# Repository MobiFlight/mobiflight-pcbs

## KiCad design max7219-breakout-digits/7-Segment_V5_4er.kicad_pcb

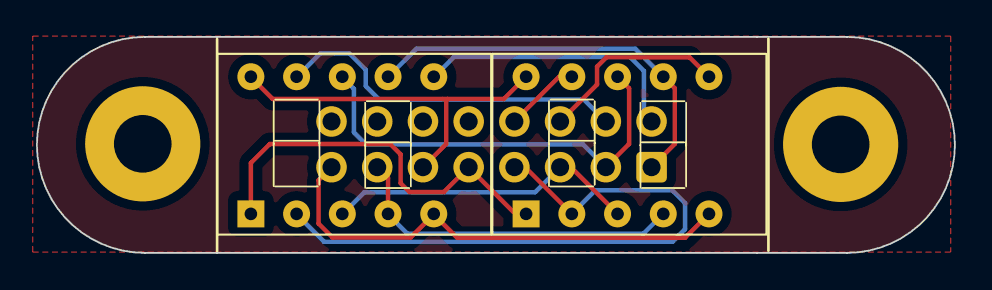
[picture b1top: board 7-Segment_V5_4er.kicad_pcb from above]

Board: 2 copper layers, 51.0 x 12.0 mm, 5 parts (1 on the bottom side), 12 nets.

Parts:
H1, H2: MountingHole 3.2mm; MountingHole_3.2mm_M3_Pad
J1: Conn_02x08_Odd_Even; IDC-Header_2x08_P2.54mm_Vertical
U1, U2: HDSM-443B_CC_2Digit_7Segment_STH; STH_7_2 Digits_0.28_CC

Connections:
/A: J1.1, U1.7 (A), U2.7 (A)
/B: J1.3, U1.8 (B), U2.8 (B)
/C: J1.5, U1.3 (C), U2.3 (C)
/D: J1.7, U1.2 (D), U2.2 (D)
/DIG0: J1.2, U2.6 (CC_DIG2)
/DIG1: J1.4, U2.9 (CC_DIG1)
/DIG2: J1.6, U1.6 (CC_DIG2)
/DIG3: J1.8, U1.9 (CC_DIG1)
/DP: J1.15, U1.5 (DP), U2.5 (DP)
/E: J1.9, U1.1 (E), U2.1 (E)
/F: J1.11, U1.10 (F), U2.10 (F)
/G: J1.13, U1.4 (G), U2.4 (G)

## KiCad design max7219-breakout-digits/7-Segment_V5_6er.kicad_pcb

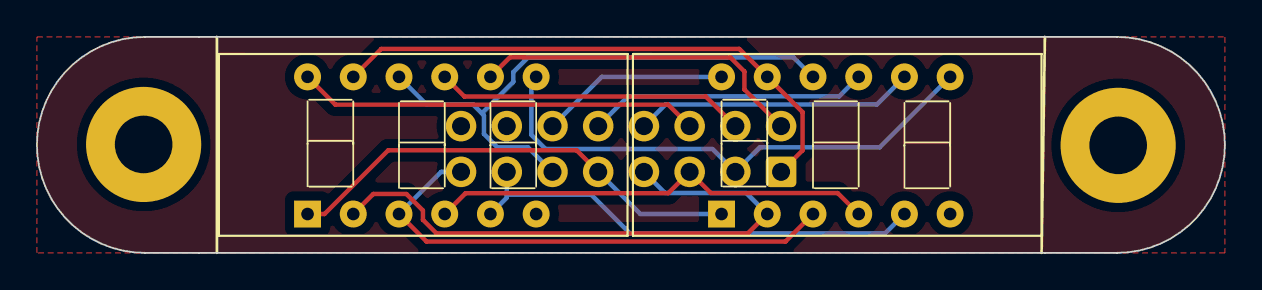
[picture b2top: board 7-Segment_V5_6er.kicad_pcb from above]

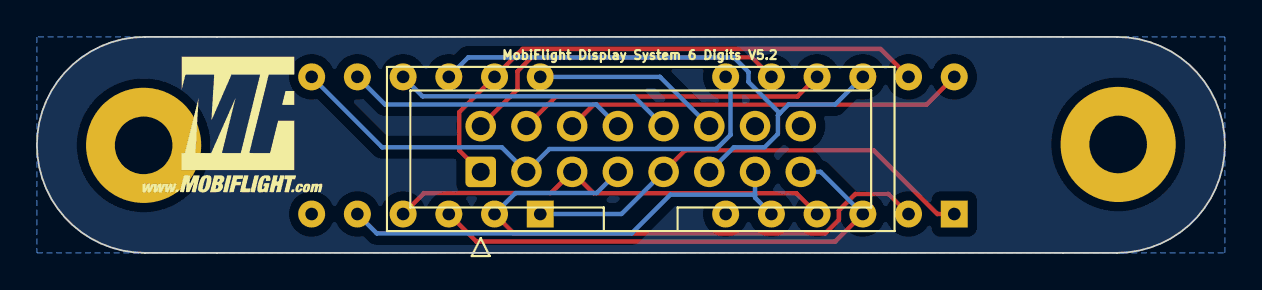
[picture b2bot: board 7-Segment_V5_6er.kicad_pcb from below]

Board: 2 copper layers, 66.0 x 12.0 mm, 6 parts (2 on the bottom side), 14 nets.

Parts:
G2: LOGO; MobiFlight-Logo-Small
H1, H2: MountingHole 3.2mm; MountingHole_3.2mm_M3_Pad
J1: Conn_02x08_Odd_Even; IDC-Header_2x08_P2.54mm_Vertical
U1, U2: 7Segment 3 digit CC_STH; STH_7_3 Digits_0.28_CC

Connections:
/A: J1.1, U1.11 (a), U2.11 (a)
/B: J1.3, U1.7 (b), U2.7 (b)
/C: J1.5, U1.4 (c), U2.4 (c)
/D: J1.7, U1.2 (d), U2.2 (d)
/DIG0: J1.2, U2.8 (CC3)
/DIG1: J1.4, U2.9 (CC2)
/DIG2: J1.6, U2.12 (CC1)
/DIG3: J1.8, U1.8 (CC3)
/DIG4: J1.10, U1.9 (CC2)
/DIG5: J1.12, U1.12 (CC1)
/DP: J1.15, U1.3 (DPX), U2.3 (DPX)
/E: J1.9, U1.1 (e), U2.1 (e)
/F: J1.11, U1.10 (f), U2.10 (f)
/G: J1.13, U1.5 (g), U2.5 (g)

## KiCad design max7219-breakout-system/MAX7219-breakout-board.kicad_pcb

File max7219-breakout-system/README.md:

# MobiFlight MAX7219 Breakout System
The MobiFlight MAX7219 Breakout System board is slightly larger than the display PCBs at 80.0 x 66.0 mm.

Since very few can get by with a MAX chip, this PCB is designed in such a way that it can accommodate up to 4 MAX chips. These chips are already connected in a daisy chain on the PCB. So no one has to worry about where the input or output is, just plug in the IN connector from the Arduino and the 4 MAX chips are connected to each other.

Since up to 8 MAX chips can be connected in a single daisy chain, this PCB was designed in such a way that a 2nd PCB can be connected easily and another 4 MAX chips are connected. Two boards connected, and the daisy chain is complete with all 8 MAX chips.

In case of space problems, this 2nd PCB can be mounted in a different location. It couldn't be easier or more comfortable.

It is therefore still possible to control up to 8 digits per MAX chip and as a daisy chain up to 8 x 8 digits, i.e. 64 digits. Since a Mega Module can control up to 4 separate MAX daisy chains, up to 4 x 64, i.e. 256 digits, are possible per Mobiflight board (e.g., [the MEGA Pro Mini](https://shop.mobiflight.com/product/arduino-mega-2560-pro-mini)).

## Connectors
There are two box headers (straight type) assigned to each MAX chip for more flexibility and efficient use.

Having two connectors allows for the possibility of dividing the 8 digits of a MAX chip between two groups of digts:
* 2 x 4 digits, 
* 1 x 3 and 1 x 5 digits,
* 1 x 6 digits, and 
* 2 x 3 digits. 

Not all 8 digits of a MAX chip have to be used. Also, the digits do not have to be distributed evenly across the MAX chips.

Between the plugs there are designations such as DIG 0-3, DIG 0-5 and DIG 4-7. This specifies how the digits are to be distributed to the plugs and thus the displays.

If, for example, 6 digits are plugged into J2, digits 0-5 are occupied. This means that digits 6 and 7 on connector J3 would remain free because, as is well known, there are no 2-digit displays in our cockpits. The smallest display unit would therefore be 3 digits.

This also applies to connectors J4 and J5, J6 and J7 and J8 and J9.

Displays with 3, 4, 5 and 6 digits can be plugged into the connectors J2, J4, J6 and J8. Displays with 3 or 4 digits can be plugged into connectors J3, J5, J7 and J9, but not more than 8 digits in total. A combination of 5 or 6 digits on J2 and 4 digits on J3 at the same time is therefore not possible.

## Prototyping board

With the 5-pin XH JST cable that is provided, a connection to the prototyping board is simple.

> [!NOTE]
> Starting with v2.0, the pin sequence is the same for both boards, the prototyping board and the MAX7219 breakout board.

## Daisy chain mode

You can connect two boards together and take advantage of the daisy chain capability. Two boards is the maximum, only up to 8 MAX7219 chips can be chained. This is a limitation of the MAX7219 chip itself.

## External Power supply
The power supply with +5V should be provided via a separate power pack, since a MAX chip can consume between 80 and 120 mA of current and thus the Mega Module or a USB interface (maximum 500 mA with USB 2.x or 900 mA with USB 3 .x) can be overloaded.

> [!NOTE]
> When using external power, set the blue jumper to the "EXT" position, otherwise use "INT" position.

## Board overview

### MAX7219 - IC1-4
The IC socket and the 4 MAX7219 chips

### Connector - J2-J9
The connectors to connect the flat ribbon cables

### IN-connectors J1+J11
The pins that are connected to pins on the MobiFlight board.

* Pin 1 - VCC
* Pin 2 - GND
* Pin 3 - DIN
* Pin 4 - CS
* PIN 5 - CLK

### OUT-connectors J10+J12
* Pin 1 - VCC
* Pin 2 - GND
* Pin 3 - DOUT
* Pin 4 - CS
* PIN 5 - CLK

## Assembly instructions
1. Solder resistors (10kOhm) to the top of the PCB
1. Solder the capacitors (100nF) to the top of the PCB
1. Solder the Max7219 IC sockets to the top of the PCB
1. Solder the XH JST connectors to the top of the PCB
1. Solder the 8x2 connectors to the top of the PCB
1. Insert the MAX7219 Chips into the sockets, watch out for correct orientation

## MobiFlight Configuration
### Device configuration
See [general documentation for more information](https://docs.mobiflight.com/devices/seven-segment-display/configuring-output/) on how to configure the 7-segment displays.

### Output config

#### Special feature with 3 digit displays
A special feature is the 3 digit displays. If 2 x 3 digits are used on connectors J2 and J3 in MobiFlight, care must be taken to ensure that they are each offset by one digit. A 3-digit display on J2 would therefore occupy digits 1, 2 and 3 in MobiFlight and on J3 digits 5, 6 and 7 in MobiFlight.

Normally, assignment of the 3 digit displays in MobiFlight when 3 digit displays are used looks like this:

With the breakout board, using two 3-digit displays looks like this:

This also applies if 5 digits are assigned to J2, then only 3 digits can be assigned to J3. But since digit 4 is parallel on J2 and J3, it is imperative to start with digit 5 on J3 for a 3-digit display (digit 5, 6 and 7). Nothing has to be taken into account when wiring, because the 3-digit PCBs already take this into account, regardless of whether they are plugged into J2 or J3.

This may look confusing at first glance, but once you look at the constellation, it quickly becomes clear that this is the only way to ensure optimum utilization without having to plug in jumpers or the like.

## Additional information

### Orientation and pin assignments

The soldering points, which are square, always designate pin 1 of the corresponding component.
After pin 1, the row continues in ascending order with pins 3, 5, 7, 9, 11, 13 and 15. The other row therefore has pins 2, 4, 6, 8, 10, 12, 14 and 16.

With the connectors J2, J4, J6 and J8 the cathodes of the displays are connected in ascending order from pin 2. So pin 2 = cathode of digit 0, pin 4 = cathode of digit 1, pin 6 = cathode 3, pin 8 = cathode 4, pin 10 = cathode 5 and pin 12 = cathode 6. Pins 14 and 16 are on the connectors always free with an even pin number.

The segments were connected to the odd pins. Pin 1 = Segment A, Pin 3 = Segment B, Pin 5 = Segment C, Pin 7 = Segment D, Pin 9 = Segment E, Pin 11 = Segment F, Pin 13 = Segment G and Pin 15 of the DP.

The situation is similar for connectors J3, J5, J7 and J9.
Pin 2 = cathode 4, pin 4 = cathode 5, pin 6 = cathode 6 and pin 8 = cathode 7. Pins 10, 12, 14 and 16 are not used.
In the case of the segments, these are assigned even numbers, as is the case with the plugs.

### Top side with components

### Bottom side

### Schematic

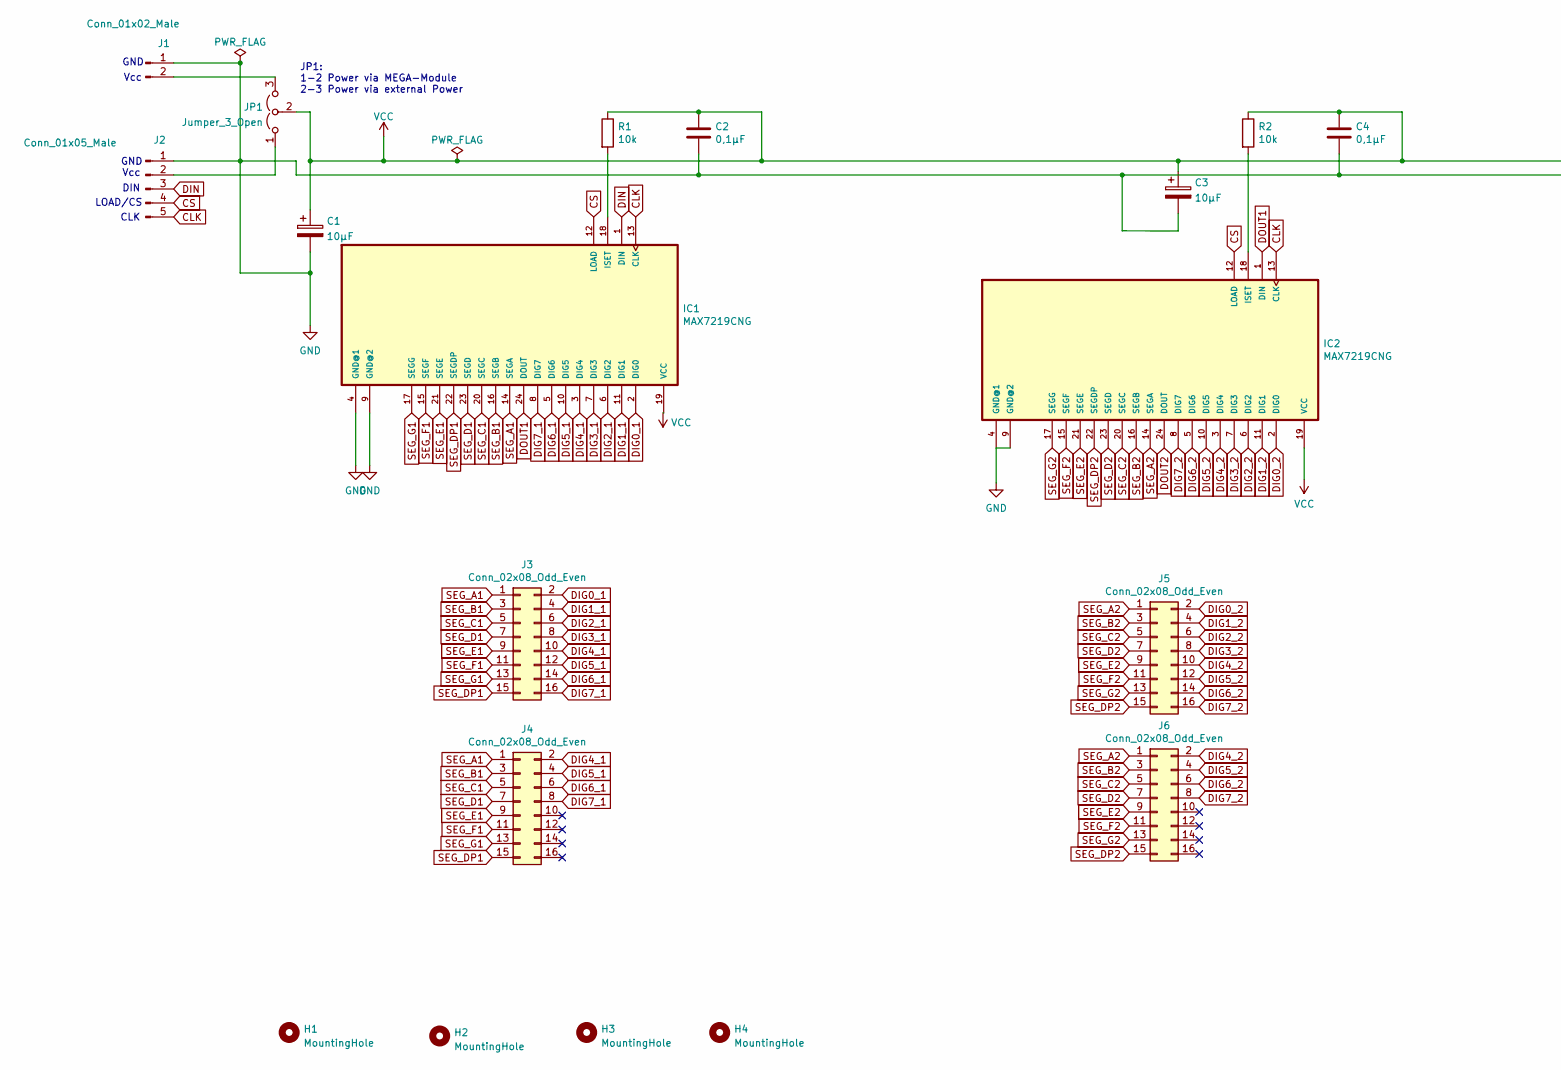
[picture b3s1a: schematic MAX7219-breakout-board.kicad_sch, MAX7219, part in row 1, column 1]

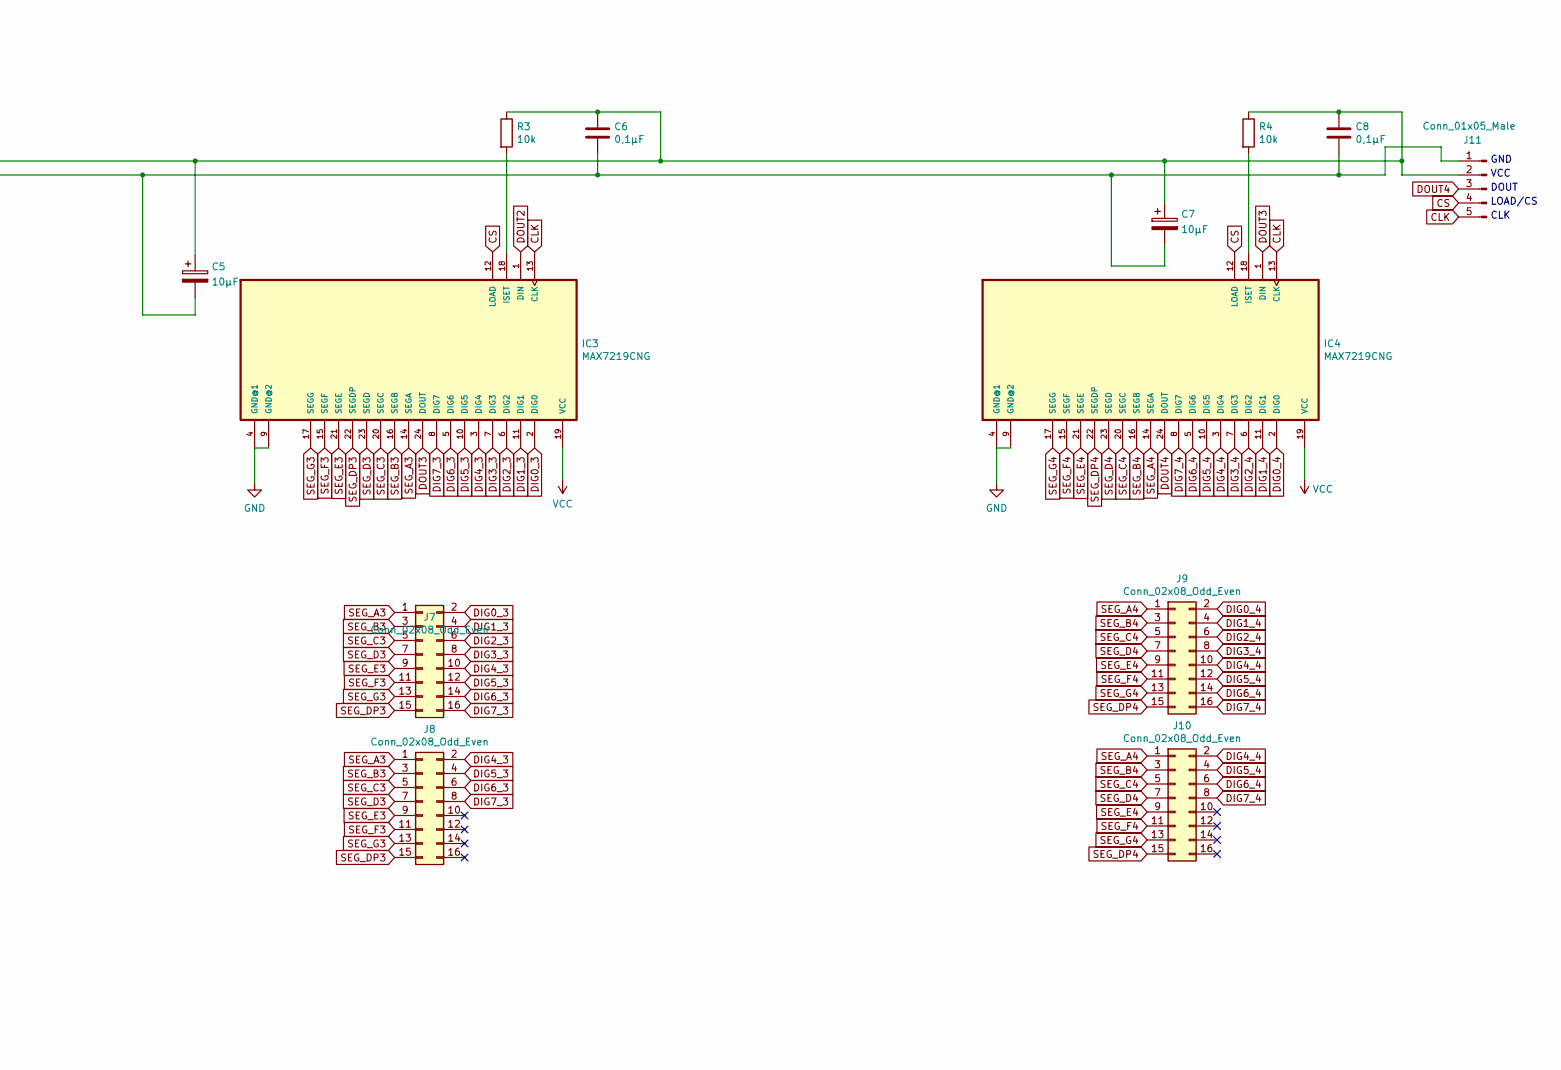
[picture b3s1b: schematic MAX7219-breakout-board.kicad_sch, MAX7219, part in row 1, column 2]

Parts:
C1, C3, C5, C7: 10µF; CP_Radial_D5.0mm_P2.50mm
C2, C4, C6, C8: 0,1µF; C_Disc_D5.0mm_W2.5mm_P5.00mm
H1, H2, H3, H4: MountingHole; MountingHole_3.2mm_M3_Pad
IC1, IC2, IC3, IC4: MAX7219CNG; DIP-24_W7.62mm
J1: Conn_01x02_Male; JST_XH_B2B-XH-A_1x02_P2.50mm_Vertical
J2, J11: Conn_01x05_Male; JST_XH_B5B-XH-A_1x05_P2.50mm_Vertical
J3, J4, J5, J6, J7, J8, J9, J10: Conn_02x08_Odd_Even; IDC-Header_2x08_P2.54mm_Vertical
JP1: Jumper_3_Open; PinHeader_1x03_P2.54mm_Vertical
R1, R2, R3, R4: 10k; R_Axial_DIN0204_L3.6mm_D1.6mm_P7.62mm_Horizontal

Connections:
CLK: IC1.13 (CLK), IC2.13 (CLK), IC3.13 (CLK), IC4.13 (CLK), J2.5, J11.5
CS: IC1.12 (LOAD), IC2.12 (LOAD), IC3.12 (LOAD), IC4.12 (LOAD), J2.4, J11.4
DIG0_1: IC1.2 (DIG0), J3.2
DIG0_2: IC2.2 (DIG0), J5.2
DIG0_3: IC3.2 (DIG0), J7.2
DIG0_4: IC4.2 (DIG0), J9.2
DIG1_1: IC1.11 (DIG1), J3.4
DIG1_2: IC2.11 (DIG1), J5.4
DIG1_3: IC3.11 (DIG1), J7.4
DIG1_4: IC4.11 (DIG1), J9.4
DIG2_1: IC1.6 (DIG2), J3.6
DIG2_2: IC2.6 (DIG2), J5.6
DIG2_3: IC3.6 (DIG2), J7.6
DIG2_4: IC4.6 (DIG2), J9.6
DIG3_1: IC1.7 (DIG3), J3.8
DIG3_2: IC2.7 (DIG3), J5.8
DIG3_3: IC3.7 (DIG3), J7.8
DIG3_4: IC4.7 (DIG3), J9.8
DIG4_1: IC1.3 (DIG4), J3.10, J4.2
DIG4_2: IC2.3 (DIG4), J5.10, J6.2
DIG4_3: IC3.3 (DIG4), J7.10, J8.2
DIG4_4: IC4.3 (DIG4), J9.10, J10.2
DIG5_1: IC1.10 (DIG5), J3.12, J4.4
DIG5_2: IC2.10 (DIG5), J5.12, J6.4
DIG5_3: IC3.10 (DIG5), J7.12, J8.4
DIG5_4: IC4.10 (DIG5), J9.12, J10.4
DIG6_1: IC1.5 (DIG6), J3.14, J4.6
DIG6_2: IC2.5 (DIG6), J5.14, J6.6
DIG6_3: IC3.5 (DIG6), J7.14, J8.6
DIG6_4: IC4.5 (DIG6), J9.14, J10.6
DIG7_1: IC1.8 (DIG7), J3.16, J4.8
DIG7_2: IC2.8 (DIG7), J5.16, J6.8
DIG7_3: IC3.8 (DIG7), J7.16, J8.8
DIG7_4: IC4.8 (DIG7), J9.16, J10.8
DIN: IC1.1 (DIN), J2.3
DOUT1: IC1.24 (DOUT), IC2.1 (DIN)
DOUT2: IC2.24 (DOUT), IC3.1 (DIN)
DOUT3: IC3.24 (DOUT), IC4.1 (DIN)
DOUT4: IC4.24 (DOUT), J11.3
GND: C1.2, C2.2, C3.2, C4.2, C5.2, C6.2, C7.2, C8.2, IC1.4 (GND@1), IC1.9 (GND@2), IC2.4 (GND@1), IC2.9 (GND@2), IC3.4 (GND@1), IC3.9 (GND@2), IC4.4 (GND@1), IC4.9 (GND@2), J1.1, J2.1, J11.1
unnamed: IC1.18 (ISET), R1.2
unnamed: IC2.18 (ISET), R2.2
unnamed: IC3.18 (ISET), R3.2
unnamed: IC4.18 (ISET), R4.2
unnamed: J1.2, JP1.3 (B)
unnamed: J2.2, JP1.1 (A)
SEG_A1: IC1.14 (SEGA), J3.1, J4.1
SEG_A2: IC2.14 (SEGA), J5.1, J6.1
SEG_A3: IC3.14 (SEGA), J7.1, J8.1
SEG_A4: IC4.14 (SEGA), J9.1, J10.1
SEG_B1: IC1.16 (SEGB), J3.3, J4.3
SEG_B2: IC2.16 (SEGB), J5.3, J6.3
SEG_B3: IC3.16 (SEGB), J7.3, J8.3
SEG_B4: IC4.16 (SEGB), J9.3, J10.3
SEG_C1: IC1.20 (SEGC), J3.5, J4.5
SEG_C2: IC2.20 (SEGC), J5.5, J6.5
SEG_C3: IC3.20 (SEGC), J7.5, J8.5
SEG_C4: IC4.20 (SEGC), J9.5, J10.5
SEG_D1: IC1.23 (SEGD), J3.7, J4.7
SEG_D2: IC2.23 (SEGD), J5.7, J6.7
SEG_D3: IC3.23 (SEGD), J7.7, J8.7
SEG_D4: IC4.23 (SEGD), J9.7, J10.7
SEG_DP1: IC1.22 (SEGDP), J3.15, J4.15
SEG_DP2: IC2.22 (SEGDP), J5.15, J6.15
SEG_DP3: IC3.22 (SEGDP), J7.15, J8.15
SEG_DP4: IC4.22 (SEGDP), J9.15, J10.15
SEG_E1: IC1.21 (SEGE), J3.9, J4.9
SEG_E2: IC2.21 (SEGE), J5.9, J6.9
SEG_E3: IC3.21 (SEGE), J7.9, J8.9
SEG_E4: IC4.21 (SEGE), J9.9, J10.9
SEG_F1: IC1.15 (SEGF), J3.11, J4.11
SEG_F2: IC2.15 (SEGF), J5.11, J6.11
SEG_F3: IC3.15 (SEGF), J7.11, J8.11
SEG_F4: IC4.15 (SEGF), J9.11, J10.11
SEG_G1: IC1.17 (SEGG), J3.13, J4.13
SEG_G2: IC2.17 (SEGG), J5.13, J6.13
SEG_G3: IC3.17 (SEGG), J7.13, J8.13
SEG_G4: IC4.17 (SEGG), J9.13, J10.13
VCC: C1.1, C2.1, C3.1, C4.1, C5.1, C6.1, C7.1, C8.1, IC1.19 (VCC), IC2.19 (VCC), IC3.19 (VCC), IC4.19 (VCC), J11.2, JP1.2 (C), R1.1, R2.1, R3.1, R4.1

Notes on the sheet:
Vcc
JP1: 1-2 Power via MEGA-Module 2-3 Power via external Power
VCC
CLK
GND
LOAD/CS
DOUT
DIN

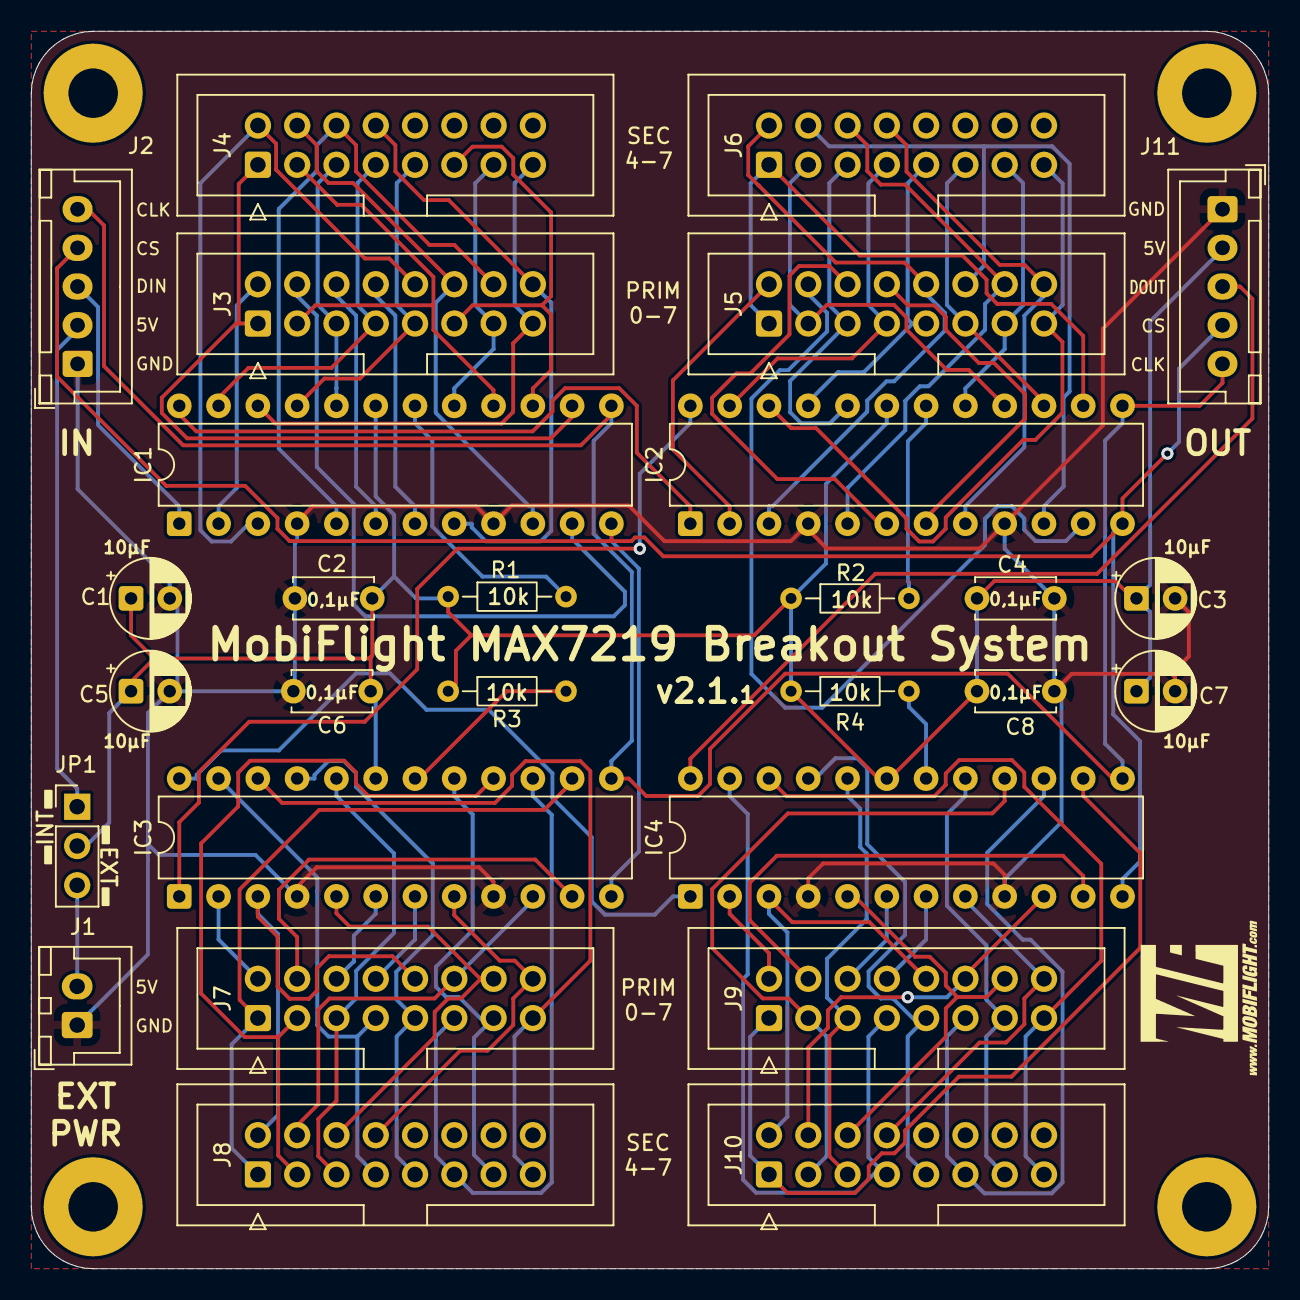
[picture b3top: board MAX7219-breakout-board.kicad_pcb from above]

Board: 2 copper layers, 80.0 x 80.0 mm, 34 parts (1 on the bottom side), 79 nets.

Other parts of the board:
G1: LOGO; MobiFlight_250x250
G2: LOGO; MobiFlight-Logo-Small

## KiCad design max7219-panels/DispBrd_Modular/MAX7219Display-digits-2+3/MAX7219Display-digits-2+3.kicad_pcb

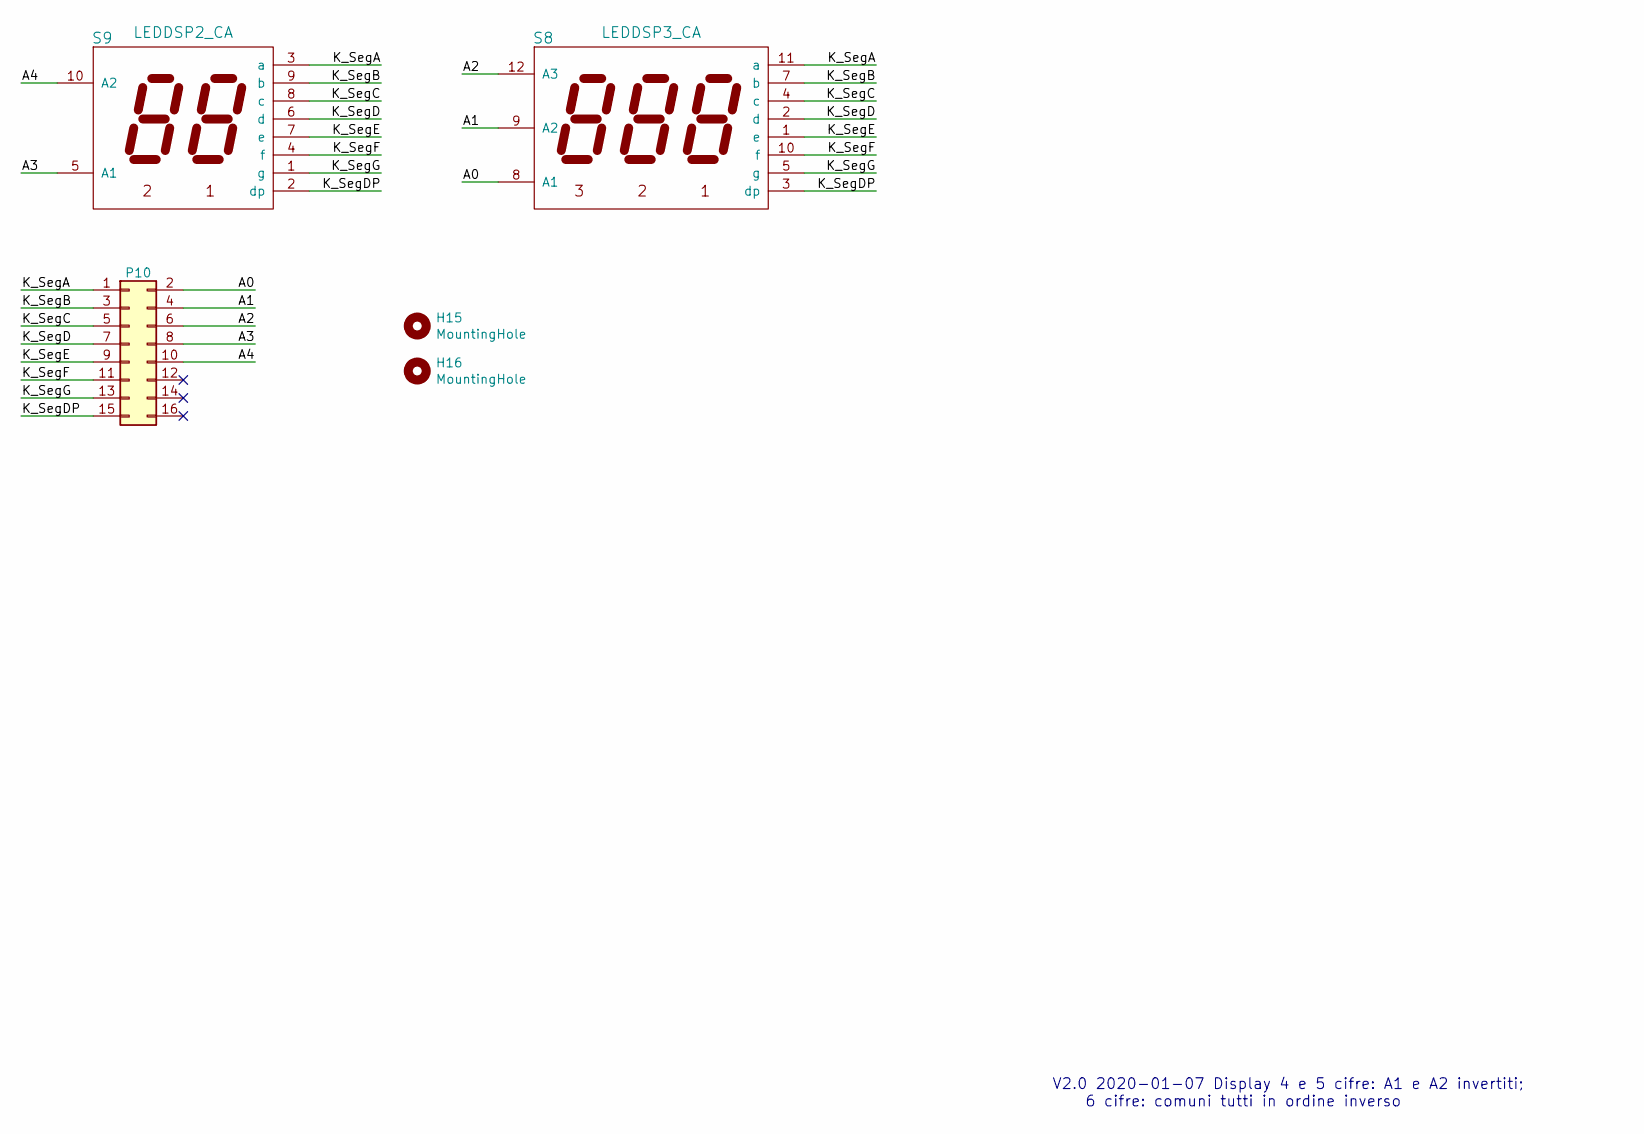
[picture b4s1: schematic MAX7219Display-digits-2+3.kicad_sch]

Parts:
H15, H16: MountingHole; Hole3mm
P10: Conn_02x08_Odd_Even; IDC-Header_2x08_P2.54mm_Vertical
S8: LEDDSP3_CA; Disp7s3x_036
S9: LEDDSP2_CA; Disp7s2x_036

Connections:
/A0: P10.2, S8.8 (A1)
/A1: P10.4, S8.9 (A2)
/A2: P10.6, S8.12 (A3)
/A3: P10.8, S9.5 (A1)
/A4: P10.10, S9.10 (A2)
/K_SegA: P10.1, S8.11 (a), S9.3 (a)
/K_SegB: P10.3, S8.7 (b), S9.9 (b)
/K_SegC: P10.5, S8.4 (c), S9.8 (c)
/K_SegD: P10.7, S8.2 (d), S9.6 (d)
/K_SegDP: P10.15, S8.3 (dp), S9.2 (dp)
/K_SegE: P10.9, S8.1 (e), S9.7 (e)
/K_SegF: P10.11, S8.10 (f), S9.4 (f)
/K_SegG: P10.13, S8.5 (g), S9.1 (g)

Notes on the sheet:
V2.0 2020-01-07 Display 4 e 5 cifre: A1 e A2 invertiti; 6 cifre: comuni tutti in ordine inverso

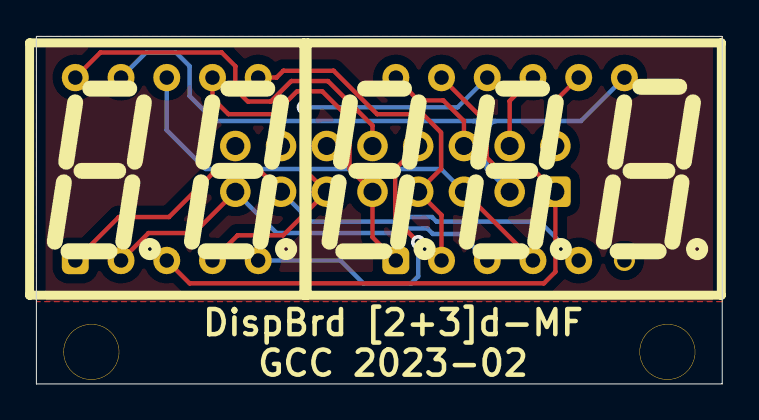
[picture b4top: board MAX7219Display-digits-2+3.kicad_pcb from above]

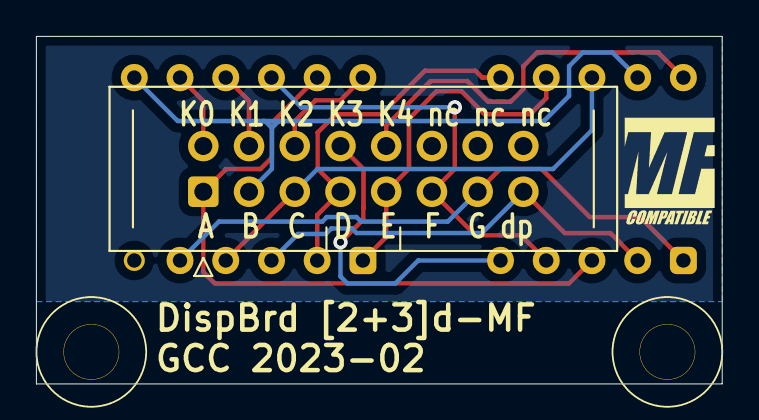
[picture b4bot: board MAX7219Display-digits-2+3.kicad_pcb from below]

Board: 2 copper layers, 38.1 x 19.3 mm, 5 parts (3 on the bottom side), 13 nets.

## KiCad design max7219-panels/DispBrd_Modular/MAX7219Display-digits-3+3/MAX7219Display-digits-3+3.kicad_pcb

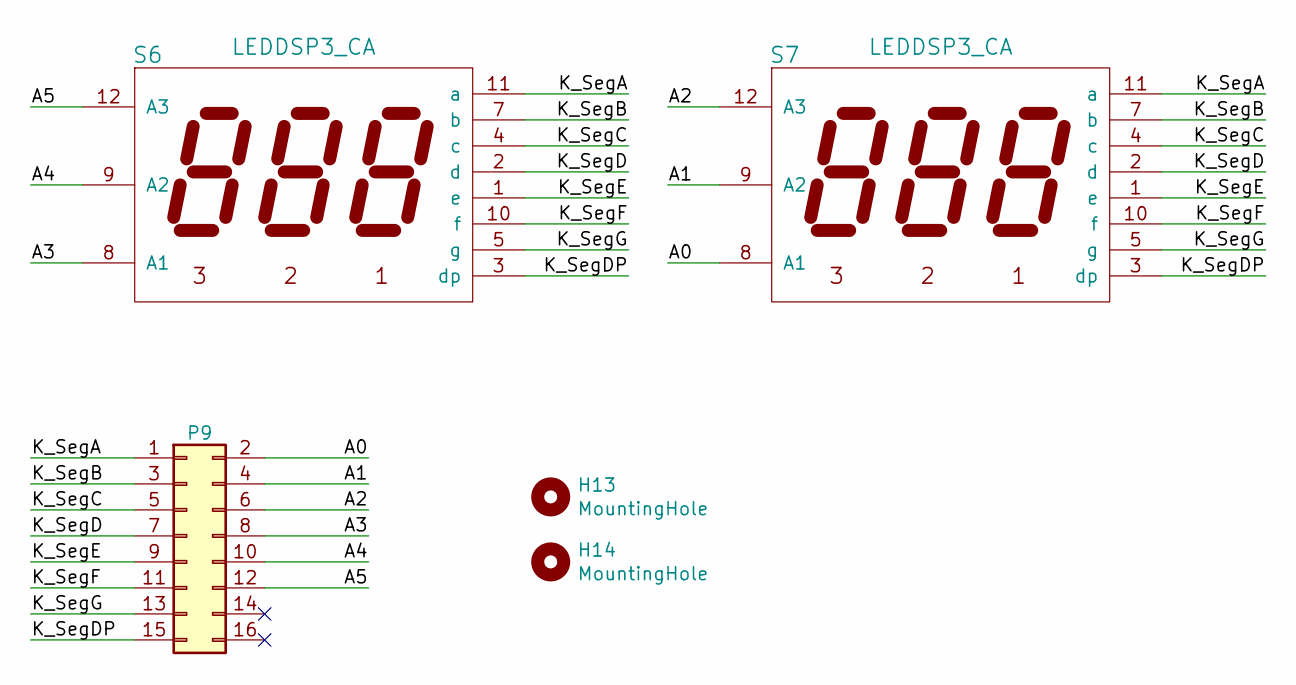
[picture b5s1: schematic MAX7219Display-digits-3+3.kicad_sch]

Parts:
H13, H14: MountingHole; Hole3mm
P9: Conn_02x08_Odd_Even; IDC-Header_2x08_P2.54mm_Vertical
S6, S7: LEDDSP3_CA; Disp7s3x_036

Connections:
/A0: P9.2, S7.8 (A1)
/A1: P9.4, S7.9 (A2)
/A2: P9.6, S7.12 (A3)
/A3: P9.8, S6.8 (A1)
/A4: P9.10, S6.9 (A2)
/A5: P9.12, S6.12 (A3)
/K_SegA: P9.1, S6.11 (a), S7.11 (a)
/K_SegB: P9.3, S6.7 (b), S7.7 (b)
/K_SegC: P9.5, S6.4 (c), S7.4 (c)
/K_SegD: P9.7, S6.2 (d), S7.2 (d)
/K_SegDP: P9.15, S6.3 (dp), S7.3 (dp)
/K_SegE: P9.9, S6.1 (e), S7.1 (e)
/K_SegF: P9.11, S6.10 (f), S7.10 (f)
/K_SegG: P9.13, S6.5 (g), S7.5 (g)

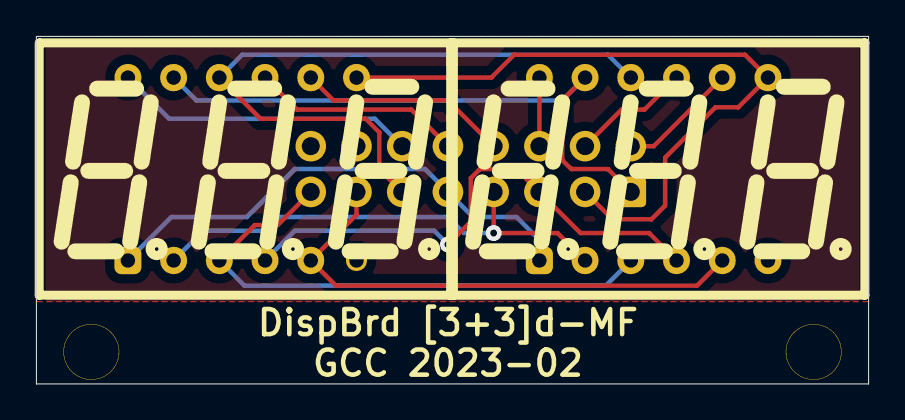
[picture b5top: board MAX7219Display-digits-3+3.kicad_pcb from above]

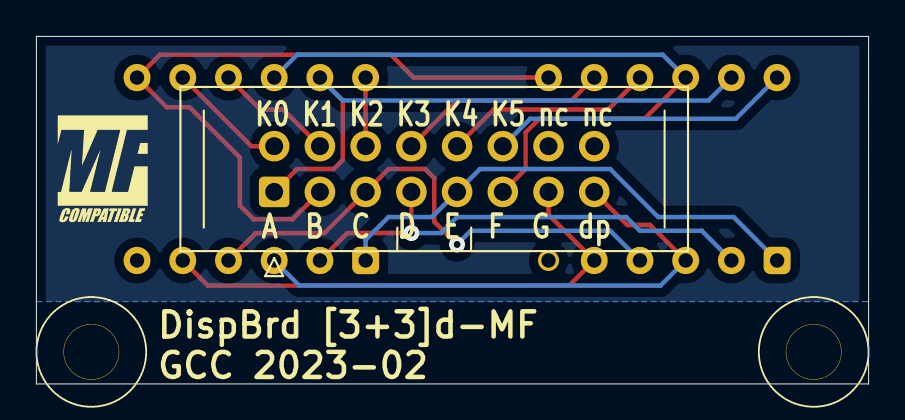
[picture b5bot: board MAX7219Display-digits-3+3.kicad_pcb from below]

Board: 2 copper layers, 46.2 x 19.3 mm, 5 parts (3 on the bottom side), 14 nets.
